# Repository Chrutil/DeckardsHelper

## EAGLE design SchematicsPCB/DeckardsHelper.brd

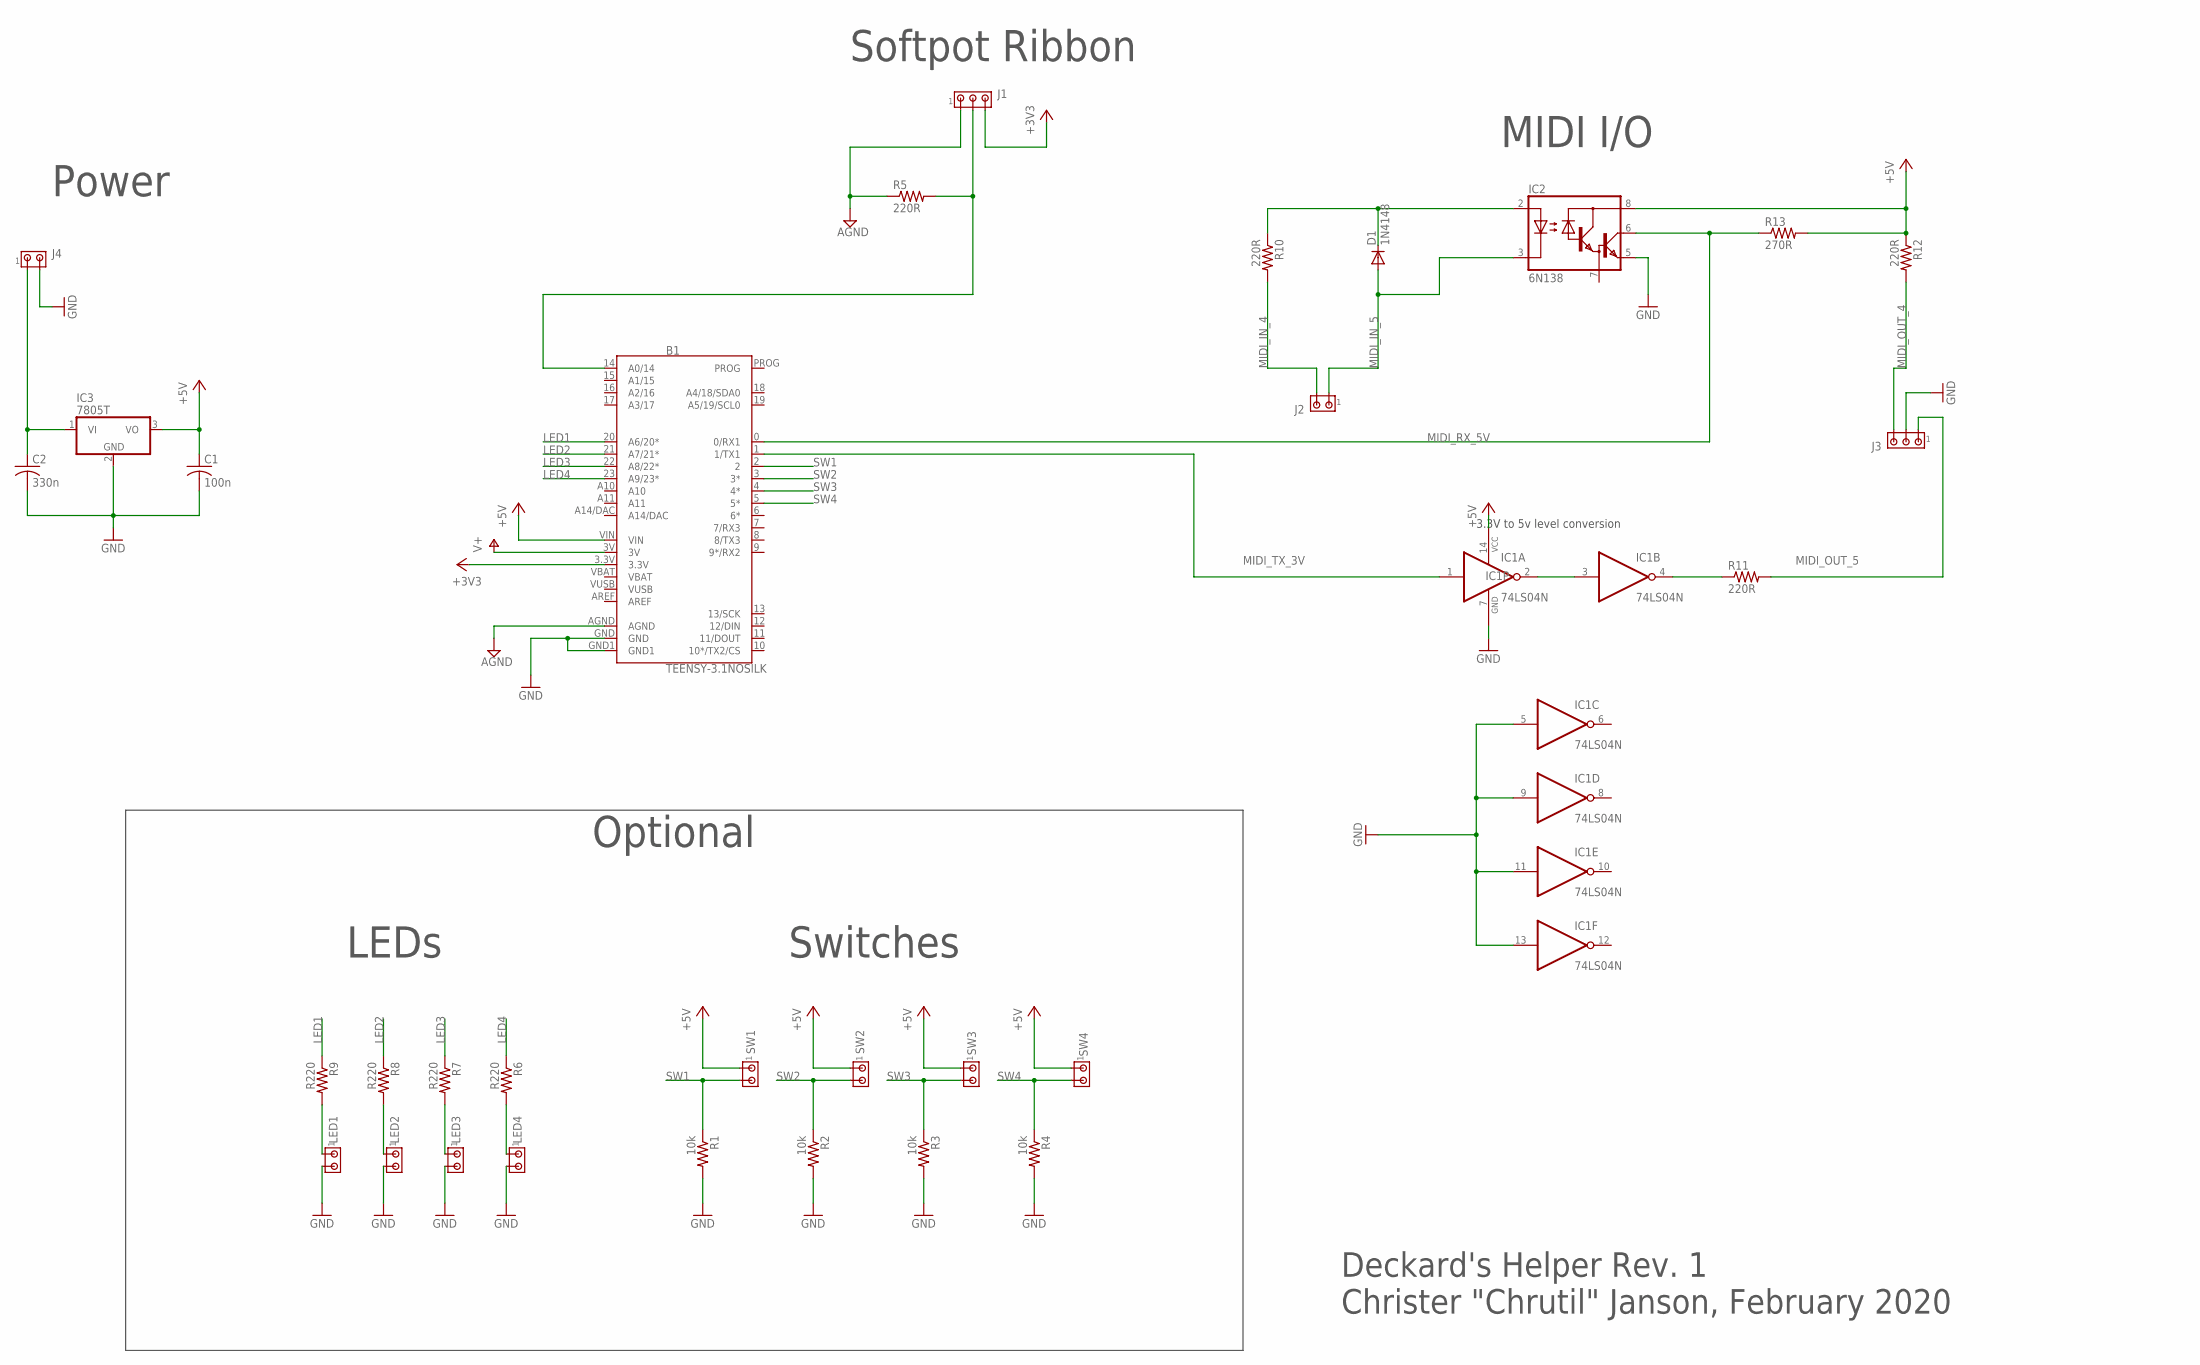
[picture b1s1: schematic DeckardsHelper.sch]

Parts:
B1: TEENSY-3.1NOSILK; TEENSY-3.1_NOSILK
C1: 100n; C025-025X050
C2: 330n; C025-025X050
D1: 1N4148; DO35-7
IC1: 74LS04N; DIL14
IC2: 6N138; DIL08
IC3: 7805T; TO220H
J1, J3: MTA03-100; 10X03MTA
J2, J4: MTA02-100; 10X02MTA
LED1, LED2, LED3, LED4: MTA02-100; 10X02MTA
R1, R2, R3, R4: 10k; 0204/7
R5, R10, R11, R12: 220R; 0204/7
R6, R7, R8, R9: R220; 0204/7
R13: 270R; 0204/7
SW1, SW2, SW3, SW4: MTA02-100; 10X02MTA

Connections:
+3V3: B1.3.3V, J1.3
+5V: B1.VIN, C1.1, IC1.14 (VCC), IC2.8 (VCC), IC3.3 (VO), R12.1, R13.2, SW1.1, SW2.1, SW3.1, SW4.1
AGND: B1.AGND, J1.1, R5.1
GND: B1.GND, B1.GND1, C1.2, C2.2, IC1.5 (I), IC1.7 (GND), IC1.9 (I), IC1.11 (I), IC1.13 (I), IC2.5 (GND), IC3.2 (GND), J3.2, J4.2, LED1.2, LED2.2, LED3.2, LED4.2, R1.2, R2.2, R3.2, R4.2
LED1: B1.20 (A6/20*), R9.1
LED2: B1.21 (A7/21*), R8.1
LED3: B1.22 (A8/22*), R7.1
LED4: B1.23 (A9/23*), R6.1
MIDI_IN_4: J2.2, R10.2
MIDI_IN_5: D1.A, IC2.3 (C), J2.1
MIDI_OUT_4: J3.3, R12.2
MIDI_OUT_5: J3.1, R11.2
MIDI_RX_5V: B1.0 (0/RX1), IC2.6 (VO), R13.1
MIDI_TX_3V: B1.1 (1/TX1), IC1.1 (I)
unnamed: IC1.2 (O), IC1.3 (I)
unnamed: IC1.4 (O), R11.1
unnamed: LED3.1, R7.2
unnamed: LED2.1, R8.2
unnamed: LED1.1, R9.2
unnamed: B1.14 (A0/14), J1.2, R5.2
unnamed: LED4.1, R6.2
unnamed: C2.1, IC3.1 (VI), J4.1
unnamed: D1.C, IC2.2 (A), R10.1
SW1: B1.2, R1.1, SW1.2
SW2: B1.3 (3*), R2.1, SW2.2
SW3: B1.4 (4*), R3.1, SW3.2
SW4: B1.5 (5*), R4.1, SW4.2
V+: B1.3V
VBAT: B1.VBAT
VUSB: B1.VUSB

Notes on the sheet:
MIDI I/O
3.3V to 5v level conversion
Softpot Ribbon
Power
LEDs
Switches
Optional
Deckard's Helper Rev. 1 Christer "Chrutil" Janson, February 2020

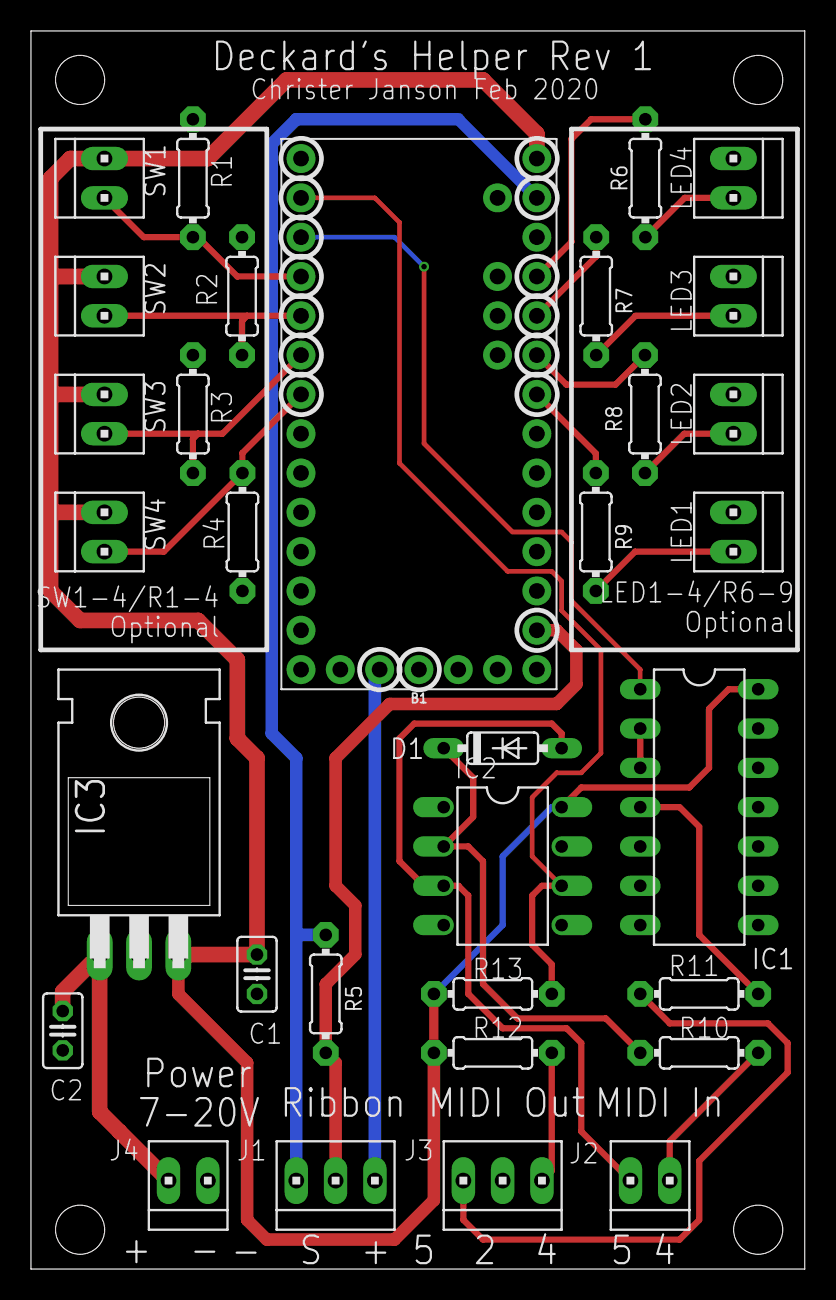
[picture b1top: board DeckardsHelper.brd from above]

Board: 2 copper layers, 50.0 x 80.0 mm, 32 parts (0 on the bottom side), 27 nets.

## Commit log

2020-02-27 Initial submission
2020-02-28 Adding Eagle Schematics and PCB and Gerber files

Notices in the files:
parts and their libraries:
SparkFun-Boards: Licensing: Creative Commons ShareAlike 4.0 International - https://creativecommons.org/licenses/by-sa/4.0
